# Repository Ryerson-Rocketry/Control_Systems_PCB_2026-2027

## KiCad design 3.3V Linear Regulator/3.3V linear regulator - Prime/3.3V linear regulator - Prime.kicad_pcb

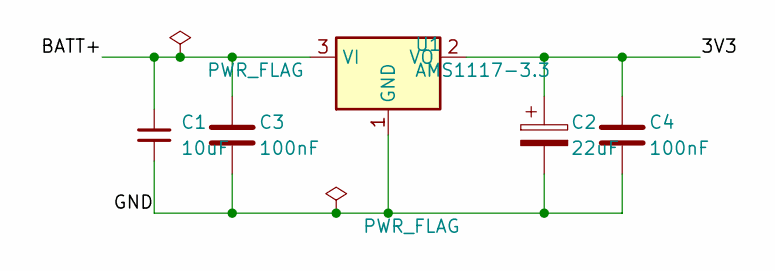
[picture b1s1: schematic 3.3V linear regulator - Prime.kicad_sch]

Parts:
C1: 10uF; C_0805_2012Metric_Pad1.18x1.45mm_HandSolder
C2: 22uF; C_0805_2012Metric_Pad1.18x1.45mm_HandSolder
C3, C4: 100nF; C_0805_2012Metric_Pad1.18x1.45mm_HandSolder
U1: AMS1117-3.3; SOT-223-3_TabPin2

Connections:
/3V3: C2.1, C4.1, U1.2 (VO)
/BATT+: C1.1, C3.1, U1.3 (VI)
/GND: C1.2, C2.2, C3.2, C4.2, U1.1 (GND)

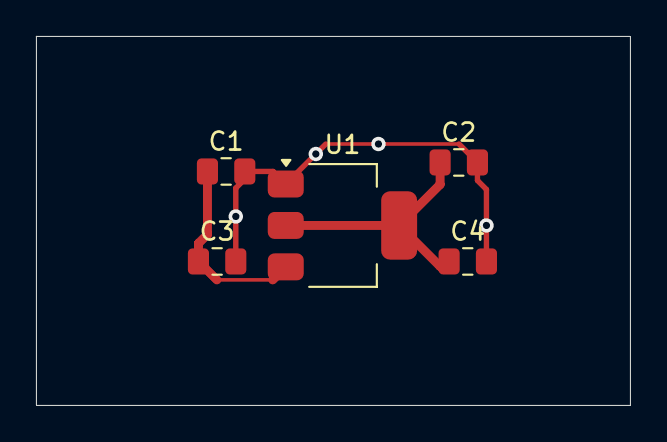
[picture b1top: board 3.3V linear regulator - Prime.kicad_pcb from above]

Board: 2 copper layers, 33.0 x 20.5 mm, 5 parts (0 on the bottom side), 3 nets.
